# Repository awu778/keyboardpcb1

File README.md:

Introduction:
PCB1 is a tenkeyless keyboard.

Technical information:
- Layout size: tenkeyless
- Compatible switches: MX style non-hotswap
- Microcontroller: ATMEGA32u4-AU
   *note: there is no compatibility with the MU variant.
- Connector: USB-C via [unified daughterboard](https://github.com/Unified-Daughterboard/)
- Firmware Compatibility: QMK (with VIA and VIAL support)
- Protection hardware: USB data line and power rail ESD suppressing, USB power overvoltage protection, Overcurrent protection

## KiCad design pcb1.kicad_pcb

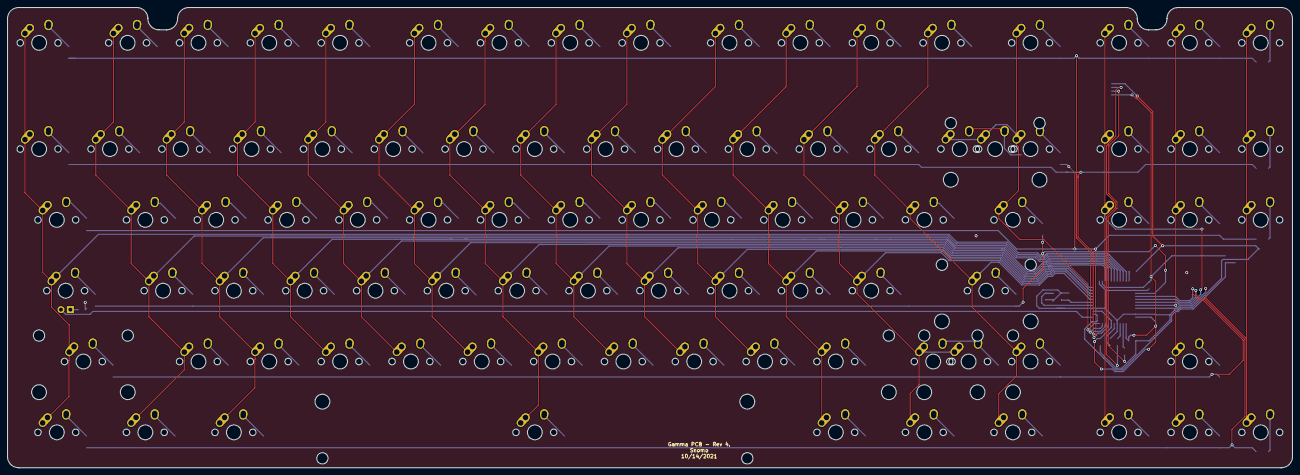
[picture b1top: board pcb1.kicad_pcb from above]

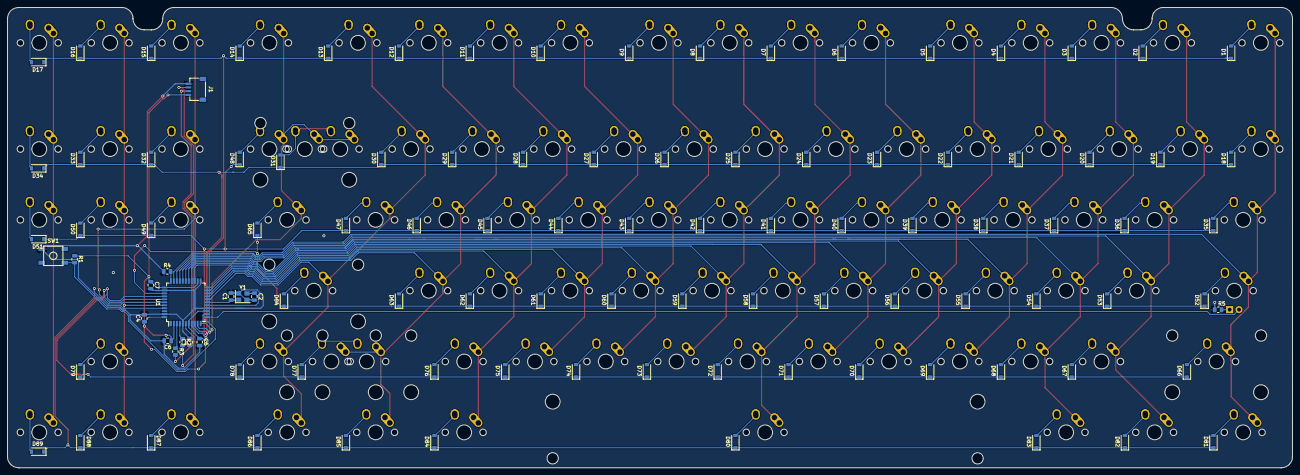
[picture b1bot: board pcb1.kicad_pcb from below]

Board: 2 copper layers, 345.6 x 123.8 mm, 196 parts (105 on the bottom side), 125 nets.

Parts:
C1, C2: 22pF; C_0805_2012Metric
C3: 1uF; C_0805_2012Metric
C4, C5, C6: 0.1uF; C_0805_2012Metric
C7: 10uF; C_0805_2012Metric
D1, D2, D3, D4, D5, D6, D7, D8, D9, D10, D11, D12, D13, D14, D15, D16, D17, D18, D19, D20, D21, D22, D23, D24, D25, D26, D27, D28, D29, D30, D31, D32, D33, D34, D35, D36, D37, D38, D39, D40, D41, D42, D43, D44, D45, D46, D47, D48, D49, D50, D51, D52, D53, D54, D55, D56, D57, D58, D59, D60, D61, D62, D63, D64, D65, D66, D67, D68, D69, D70, D71, D72, D73, D74, D75, D76, D77, D78, D79, D80, D82, D83, D84, D85, D86, D87, D88, D89: SOD_123; D_SOD-123
D81: D_Small; D_SOD-123
J1: Connector_Generic_Conn_01x04; JST-SR-4
MX1: Esc; MX-1U-NoLED
MX2: F1; MX-1U-NoLED
MX3: F2; MX-1U-NoLED
MX4: F3; MX-1U-NoLED
MX5: F4; MX-1U-NoLED
MX6: F5; MX-1U-NoLED
MX7: F6; MX-1U-NoLED
MX8: F7; MX-1U-NoLED
MX9: F8; MX-1U-NoLED
MX10: F9; MX-1U-NoLED
MX11: F10; MX-1U-NoLED
MX12: F11; MX-1U-NoLED
MX13: F12; MX-1U-NoLED
MX14: F13; MX-1U-NoLED
MX15: PrtSc; MX-1U-NoLED
MX16: Scroll Lc; MX-1U-NoLED
MX17: Pause; MX-1U-NoLED
MX18: `; MX-1U-NoLED
MX19: 1; MX-1U-NoLED
MX20: 2; MX-1U-NoLED
MX21: 3; MX-1U-NoLED
MX22: 4; MX-1U-NoLED
MX23: 5; MX-1U-NoLED
MX24: 6; MX-1U-NoLED
MX25: 7; MX-1U-NoLED
MX26: 8; MX-1U-NoLED
MX27: 9; MX-1U-NoLED
MX28: 0; MX-1U-NoLED
MX29: -; MX-1U-NoLED
MX30: =; MX-1U-NoLED
MX31: BcSpc; MX-1U-NoLED
MX31#2: BcSpc; MX-2U-NoLED
MX32: Insert; MX-1U-NoLED
MX33: Home; MX-1U-NoLED
MX34: Pg Up; MX-1U-NoLED
MX35: Tab; MX-1.5U-NoLED
MX36: Q; MX-1U-NoLED
MX37: W; MX-1U-NoLED
MX38: E; MX-1U-NoLED
MX39: R; MX-1U-NoLED
MX40: T; MX-1U-NoLED
MX41: Y; MX-1U-NoLED
MX42: U; MX-1U-NoLED
MX43: I; MX-1U-NoLED
MX44: O; MX-1U-NoLED
MX45: P; MX-1U-NoLED
MX46: [; MX-1U-NoLED
MX47: ]; MX-1U-NoLED
MX48: BcSpc1; MX-1U-NoLED
MX49: Delete; MX-1U-NoLED
MX50: End; MX-1U-NoLED
MX51: Pg Dn; MX-1U-NoLED
MX52: Caps; MX-1.5U
MX53: A; MX-1U-NoLED
MX54: S; MX-1U-NoLED
MX55: D; MX-1U-NoLED
MX56: F; MX-1U-NoLED
MX57: G; MX-1U-NoLED
MX58: H; MX-1U-NoLED
MX59: J; MX-1U-NoLED
MX60: K; MX-1U-NoLED
MX61: L; MX-1U-NoLED
MX62: ;; MX-1U-NoLED
MX63: '; MX-1U-NoLED
MX64: Enter; MX-2.25U-NoLED
MX65: Pipe; MX-1.5U-NoLED
MX66: L Shift; MX-2.75U-NoLED
MX67: Z; MX-1U-NoLED
MX68: X; MX-1U-NoLED
MX69: C; MX-1U-NoLED
MX70: V; MX-1U-NoLED
MX71: B; MX-1U-NoLED
MX72: N; MX-1U-NoLED
MX73: M; MX-1U-NoLED
MX74: ,; MX-1U-NoLED
MX75: .; MX-1U-NoLED
MX76: /; MX-1U-NoLED
MX77, MX77#2: R Shift; MX-2.75U-NoLED
MX78: R Shift1; MX-1U-NoLED
MX79: Up; MX-1U-NoLED
MX80: Space; MX-7U-ReversedStabilizers-NoLED
MX81, MX86: Ctrl; MX-1.5U-NoLED
MX82, MX85: Win; MX-1U-NoLED
MX83, MX84: Alt; MX-1.5U-NoLED
MX87: Left; MX-1U-NoLED
MX88: Down; MX-1U-NoLED
MX89: Right; MX-1U-NoLED
R1: 10k; R_0805_2012Metric
R2, R3: 22; R_0805_2012Metric
R4: 10K; R_0805_2012Metric
R5: 1.5k; R_0805_2012Metric
SW1: SW_Push; SKQG-1155865
U1: ATmega32U4-AU; TQFP-44_10x10mm_P0.8mm
Y1: 16MHz; Crystal_SMD_3225-4Pin_3.2x2.5mm

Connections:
+5V: C4.1, C5.1, C6.1, C7.1, J1.1, R1.1, U1.2, U1.7, U1.14, U1.24, U1.34, U1.44
Col0: MX1.1, MX18.1, MX35.1, MX52.1, MX66.1, MX81.1, U1.32
Col1: MX2.1, MX19.1, MX36.1, MX53.1, MX67.1, MX82.1, U1.31
Col2: MX3.1, MX20.1, MX37.1, MX54.1, MX68.1, MX83.1, U1.30
Col3: MX4.1, MX21.1, MX38.1, MX55.1, MX69.1, U1.29
Col4: MX5.1, MX22.1, MX39.1, MX56.1, MX70.1, U1.28
Col5: MX6.1, MX23.1, MX40.1, MX57.1, MX71.1, U1.27
Col6: MX7.1, MX24.1, MX41.1, MX58.1, MX72.1, MX80.1, U1.26
Col7: MX8.1, MX25.1, MX42.1, MX59.1, MX73.1, U1.25
Col8: MX9.1, MX26.1, MX43.1, MX60.1, MX74.1, U1.22
Col9: MX10.1, MX27.1, MX44.1, MX61.1, MX75.1, U1.21
Col10: MX11.1, MX28.1, MX45.1, MX62.1, MX76.1, MX84.1, U1.20
Col11: MX12.1, MX29.1, MX46.1, MX63.1, MX77.1, MX77#2.1, MX85.1, U1.19
Col12: MX13.1, MX30.1, MX47.1, MX64.1, MX78.1, MX86.1, U1.18
Col13: MX14.1, MX31.1, MX31#2.1, MX48.1, MX65.1, U1.11
Col14: MX15.1, MX32.1, MX49.1, MX87.1, U1.39
Col15: MX16.1, MX33.1, MX50.1, MX79.1, MX88.1, U1.40
Col16: MX17.1, MX34.1, MX51.1, MX89.1, U1.41
D+: J1.3, R2.2
D-: J1.2, R3.2
GND: C1.2, C2.2, C3.2, C4.2, C5.2, C6.2, C7.2, J1.4, R4.1, R5.1, SW1.1, U1.5, U1.15, U1.23, U1.35, U1.43, Y1.2, Y1.4
LEDout: MX52.4, R5.2
Led: MX52.3, U1.12
unnamed: C1.1, U1.17, Y1.1
unnamed: C2.1, U1.16, Y1.3
unnamed: C3.1, U1.6
unnamed: D1.2, MX1.2
unnamed: D2.2, MX2.2
unnamed: D3.2, MX3.2
unnamed: D4.2, MX4.2
unnamed: D5.2, MX5.2
unnamed: D6.2, MX6.2
unnamed: D7.2, MX7.2
unnamed: D8.2, MX8.2
unnamed: D9.2, MX9.2
unnamed: D10.2, MX10.2
unnamed: D11.2, MX11.2
unnamed: D12.2, MX12.2
unnamed: D13.2, MX13.2
unnamed: D14.2, MX14.2
unnamed: D15.2, MX15.2
unnamed: D16.2, MX16.2
unnamed: D17.2, MX17.2
unnamed: D18.2, MX18.2
unnamed: D19.2, MX19.2
unnamed: D20.2, MX20.2
unnamed: D21.2, MX21.2
unnamed: D22.2, MX22.2
unnamed: D23.2, MX23.2
unnamed: D24.2, MX24.2
unnamed: D25.2, MX25.2
unnamed: D26.2, MX26.2
unnamed: D27.2, MX27.2
unnamed: D28.2, MX28.2
unnamed: D29.2, MX29.2
unnamed: D30.2, MX30.2
unnamed: D31.2, MX31.2, MX31#2.2
unnamed: D32.2, MX32.2
unnamed: D33.2, MX33.2
unnamed: D34.2, MX34.2
unnamed: D35.2, MX35.2
unnamed: D36.2, MX36.2
unnamed: D37.2, MX37.2
unnamed: D38.2, MX38.2
unnamed: D39.2, MX39.2
unnamed: D40.2, MX40.2
unnamed: D41.2, MX41.2
unnamed: D42.2, MX42.2
unnamed: D43.2, MX43.2
unnamed: D44.2, MX44.2
unnamed: D45.2, MX45.2
unnamed: D46.2, MX46.2
unnamed: D47.2, MX47.2
unnamed: D48.2, MX48.2
unnamed: D49.2, MX49.2
unnamed: D50.2, MX50.2
unnamed: D51.2, MX51.2
unnamed: D52.2, MX52.2
unnamed: D53.2, MX53.2
unnamed: D54.2, MX54.2
unnamed: D55.2, MX55.2
unnamed: D56.2, MX56.2
unnamed: D57.2, MX57.2
unnamed: D58.2, MX58.2
unnamed: D59.2, MX59.2
unnamed: D60.2, MX60.2
unnamed: D61.2, MX61.2
unnamed: D62.2, MX62.2
unnamed: D63.2, MX63.2
unnamed: D64.2, MX64.2
unnamed: D65.2, MX65.2
unnamed: D66.2, MX66.2
unnamed: D67.2, MX67.2
unnamed: D68.2, MX68.2
unnamed: D69.2, MX69.2
unnamed: D70.2, MX70.2
unnamed: D71.2, MX71.2
unnamed: D72.2, MX72.2
unnamed: D73.2, MX73.2
unnamed: D74.2, MX74.2
unnamed: D75.2, MX75.2
unnamed: D76.2, MX76.2
unnamed: D77.2, MX77.2, MX77#2.2
unnamed: D78.2, MX78.2
unnamed: D79.2, MX79.2
unnamed: D80.2, MX80.2
unnamed: D81.2, MX81.2
unnamed: D82.2, MX82.2
unnamed: D83.2, MX83.2
unnamed: D84.2, MX84.2
unnamed: D85.2, MX85.2
unnamed: D86.2, MX86.2
unnamed: D87.2, MX87.2
unnamed: D88.2, MX88.2
unnamed: D89.2, MX89.2
unnamed: R1.2, SW1.2, U1.13
unnamed: R2.1, U1.4
unnamed: R3.1, U1.3
unnamed: R4.2, U1.33
Row0: D1.1, D2.1, D3.1, D4.1, D5.1, D6.1, D7.1, D8.1, D9.1, D10.1, D11.1, D12.1, D13.1, D14.1, D15.1, D16.1, D17.1, U1.10
Row1: D18.1, D19.1, D20.1, D21.1, D22.1, D23.1, D24.1, D25.1, D26.1, D27.1, D28.1, D29.1, D30.1, D31.1, D32.1, D33.1, D34.1, U1.9
Row2: D35.1, D36.1, D37.1, D38.1, D39.1, D40.1, D41.1, D42.1, D43.1, D44.1, D45.1, D46.1, D47.1, D48.1, D49.1, D50.1, D51.1, U1.8
Row3: D52.1, D53.1, D54.1, D55.1, D56.1, D57.1, D58.1, D59.1, D60.1, D61.1, D62.1, D63.1, D64.1, D65.1, U1.36
Row4: D66.1, D67.1, D68.1, D69.1, D70.1, D71.1, D72.1, D73.1, D74.1, D75.1, D76.1, D77.1, D78.1, D79.1, U1.37
Row5: D80.1, D81.1, D82.1, D83.1, D84.1, D85.1, D86.1, D87.1, D88.1, D89.1, U1.38

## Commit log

2024-05-08 Create image
